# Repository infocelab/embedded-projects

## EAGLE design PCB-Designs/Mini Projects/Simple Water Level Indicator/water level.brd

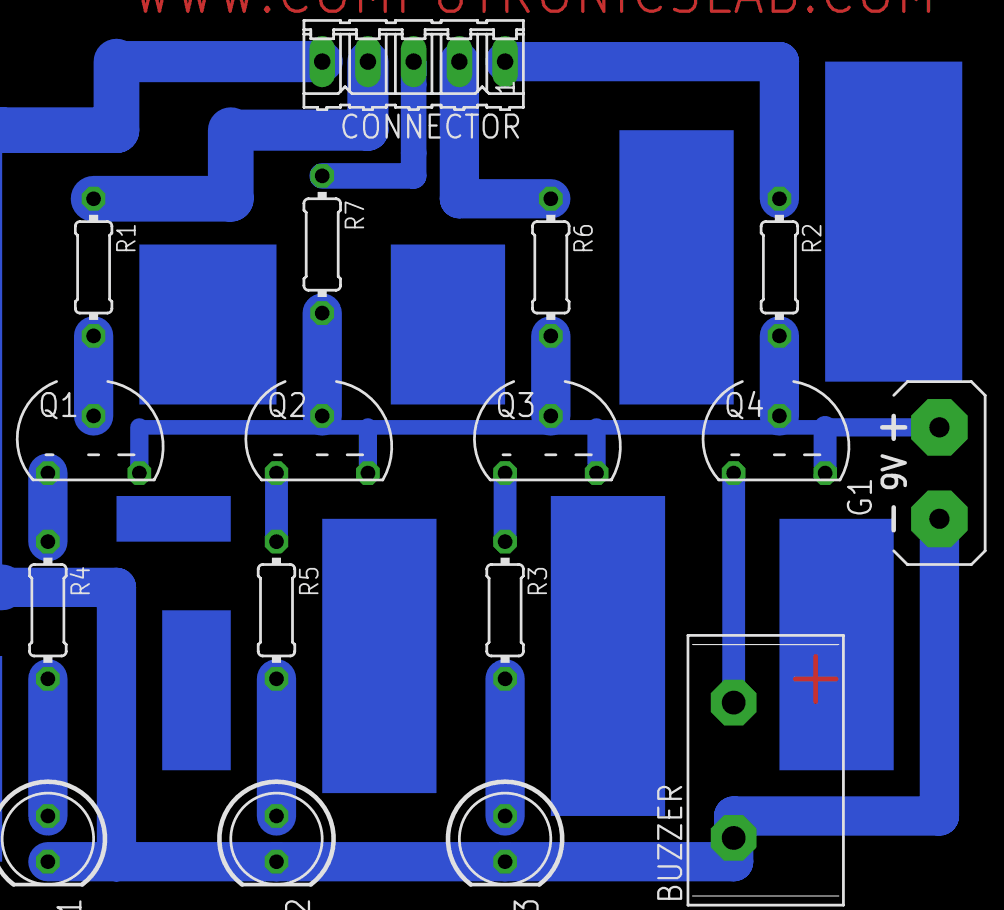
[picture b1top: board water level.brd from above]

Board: 2 copper layers, 17 parts (0 on the bottom side), 17 nets.

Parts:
BUZZER: B/C11S
CONNECTOR: 05P
G1: AB9V
LED1, LED2, LED3: 5mm; LED5MM
Q1, Q2, Q3, Q4: BC557; TO92
R1, R2, R3, R4, R5, R6, R7: 470E; 0204/7

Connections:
unnamed: Q1.3, R4.1
unnamed: Q2.3, R5.1
unnamed: Q3.3, R3.1
unnamed: Q1.2, R1.2
unnamed: Q2.2, R7.2
unnamed: Q3.2, R6.2
unnamed: Q4.2, R2.2
unnamed: BUZZER.2, Q4.3
unnamed: LED1.A, R4.2
unnamed: LED3.A, R3.2
unnamed: G1.+, Q1.1, Q2.1, Q3.1, Q4.1
unnamed: BUZZER.1, CONNECTOR.5, G1.-, LED1.K, LED2.K, LED3.K
unnamed: CONNECTOR.2, R6.1
unnamed: CONNECTOR.3, R7.1
unnamed: CONNECTOR.4, R1.1
unnamed: CONNECTOR.1, R2.1
unnamed: LED2.A, R5.2

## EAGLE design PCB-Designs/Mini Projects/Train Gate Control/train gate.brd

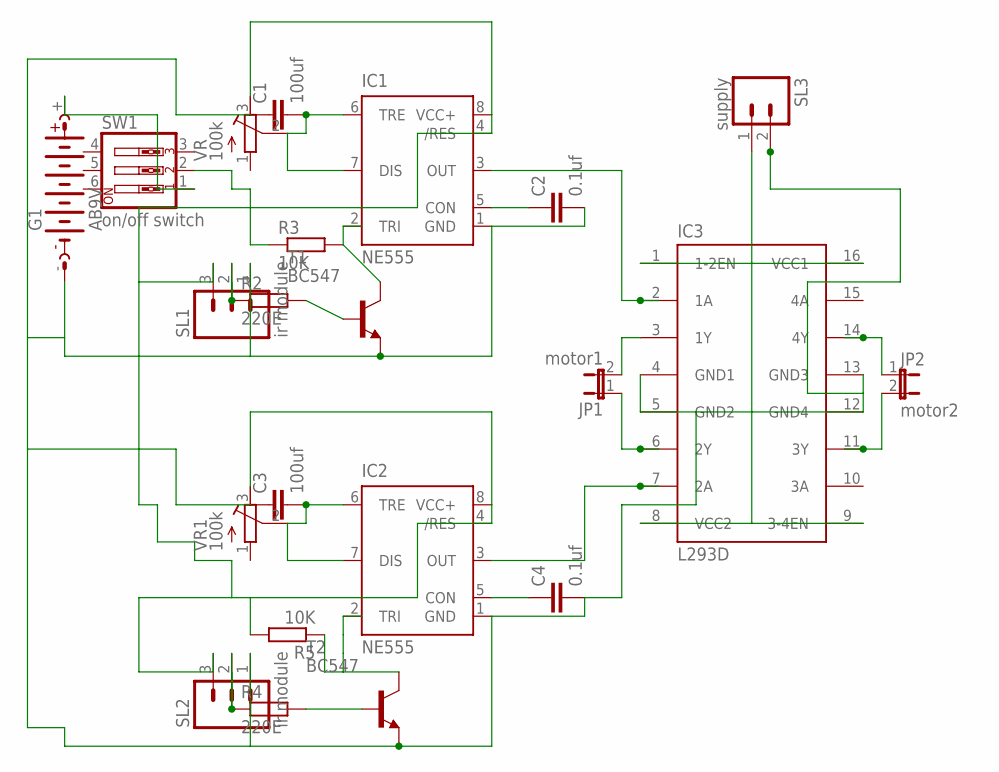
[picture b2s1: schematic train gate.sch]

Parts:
C1, C3: 100uf; C5B7.2
C2, C4: 0.1uf; C2.5-3
G1: AB9V
IC1, IC2: NE555; DIL-08
IC3: L293D; DIL16
JP1: motor1; JP1
JP2: motor2; JP1
R2, R4: 220E; 0204/7
R3, R5: 10K; 0204/7
SL1, SL2: ir module; 03P
SL3: supply; 02P
SW1: on/off switch; EDG-03
T1, T2: BC547; TO92
VR, VR1: 100k; RTRIM64P

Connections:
unnamed: C1.2, IC1.6 (TRE), IC1.7 (DIS), VR.2 (S)
unnamed: C3.2, IC2.6 (TRE), IC2.7 (DIS), VR1.2 (S)
unnamed: R2.1, SL1.2
unnamed: R4.1, SL2.2
unnamed: C2.1, IC1.5 (CON)
unnamed: R4.2, T2.2 (B)
unnamed: G1.+, SW1.1
unnamed: IC1.2 (TRI), R3.2, T1.3 (C)
unnamed: C4.1, IC2.5 (CON)
unnamed: IC2.2 (TRI), R5.1, T2.3 (C)
unnamed: C1.1, C2.2, C3.1, C4.2, G1.-, IC1.1 (GND), IC2.1 (GND), IC3.4 (GND1), IC3.5 (GND2), IC3.12 (GND4), IC3.13 (GND3), SL1.1, SL2.1, SL3.2, T1.1 (E), T2.1 (E)
unnamed: IC3.1 (1-2EN), IC3.8 (VCC2), IC3.9 (3-4EN), IC3.16 (VCC1), SL3.1
unnamed: IC1.4 (/RES), IC1.8 (VCC+), IC2.4 (/RES), IC2.8 (VCC+), R3.1, R5.2, SL1.3, SL2.3, SW1.2, VR.3 (A), VR1.3 (A)
unnamed: R2.2, T1.2 (B)
unnamed: IC3.3 (1Y), JP1.2
unnamed: IC3.6 (2Y), JP1.1
unnamed: IC3.14 (4Y), JP2.1
unnamed: IC3.11 (3Y), JP2.2
unnamed: IC1.3 (OUT), IC3.2 (1A)
unnamed: IC2.3 (OUT), IC3.7 (2A)

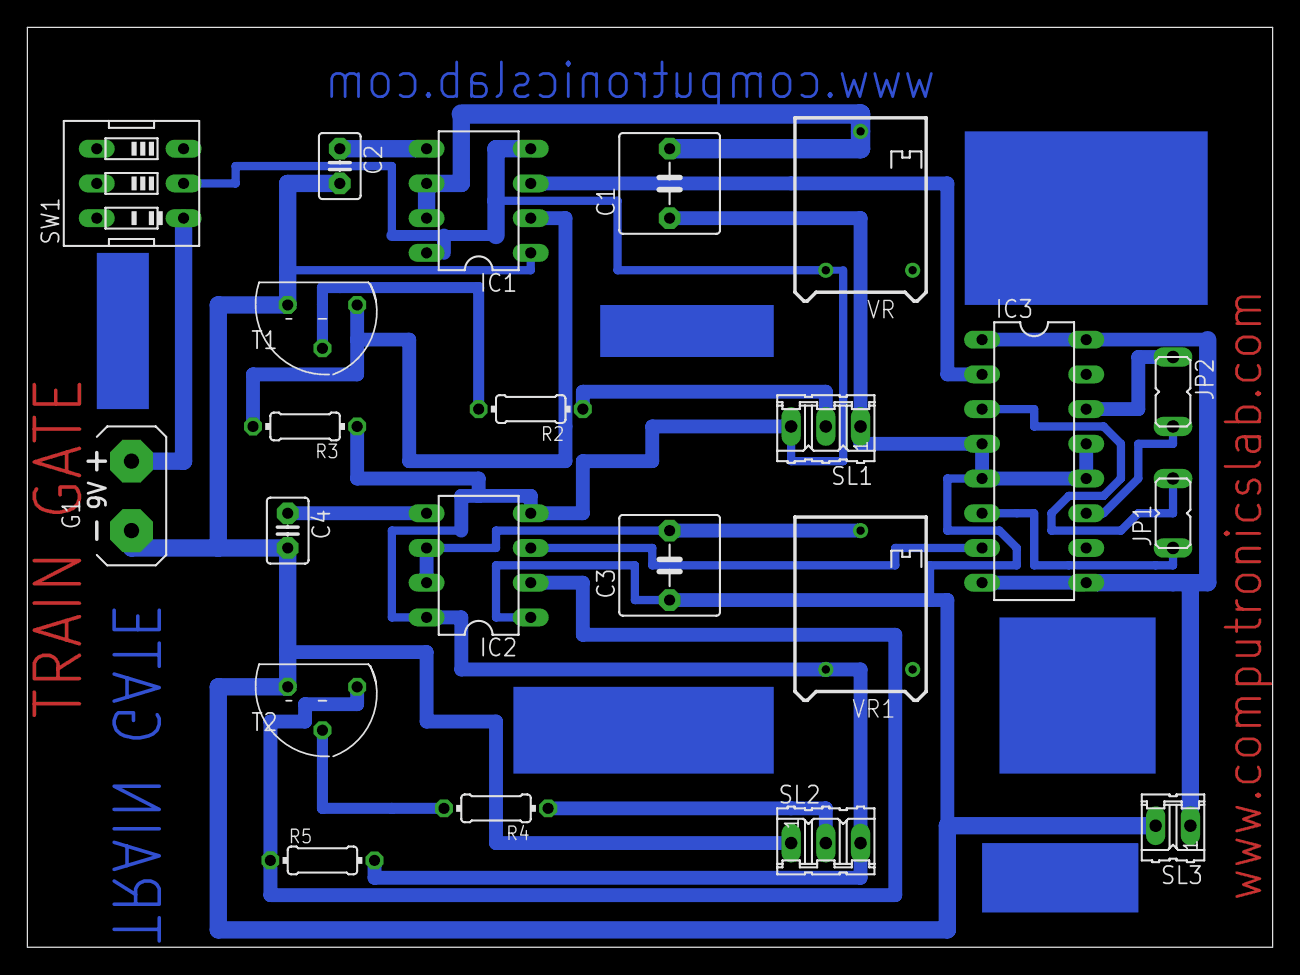
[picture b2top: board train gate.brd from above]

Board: 2 copper layers, 91.1 x 67.3 mm, 22 parts (0 on the bottom side), 20 nets.

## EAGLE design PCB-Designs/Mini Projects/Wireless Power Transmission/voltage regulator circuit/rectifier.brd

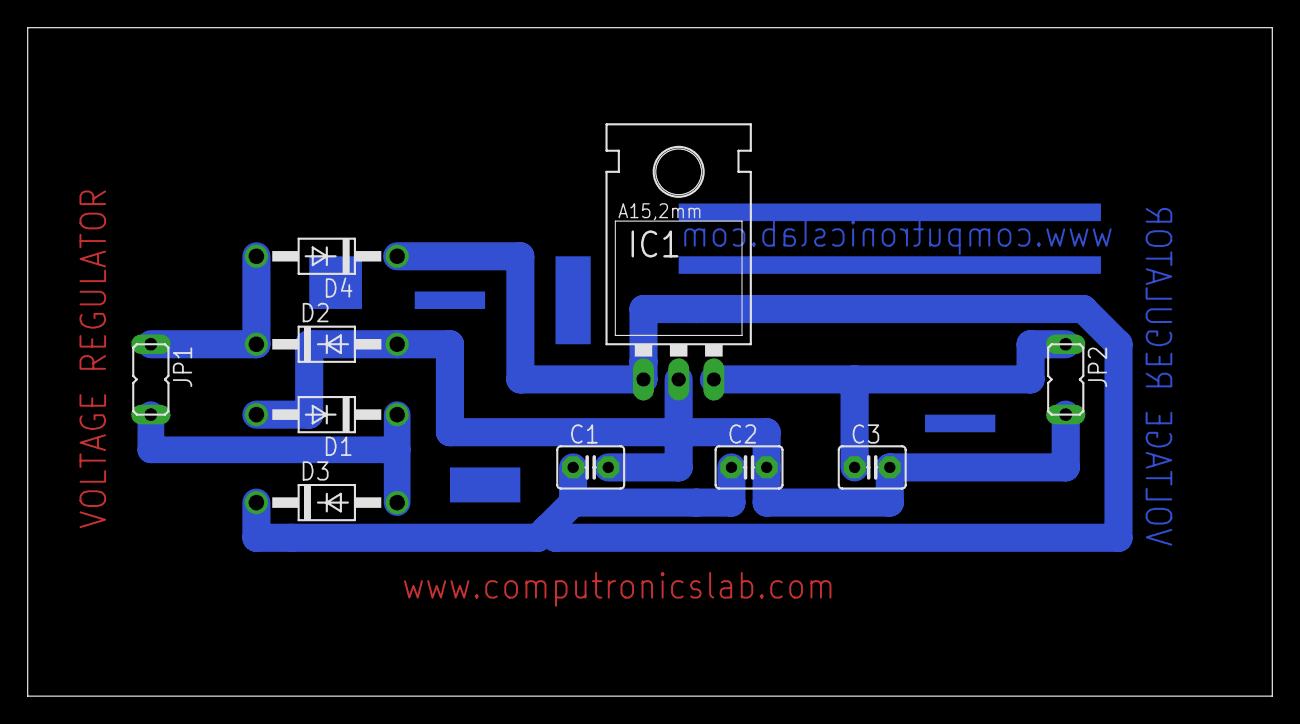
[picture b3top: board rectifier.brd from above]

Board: 2 copper layers, 89.8 x 48.2 mm, 10 parts (0 on the bottom side), 5 nets.

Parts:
C1: 47uf; C2.5-3
C2, C3: 0.1uf; C2.5-3
D1, D2, D3, D4: 1N4007; DO41-10
IC1: 7805; 78XXL
JP1: transformer; JP1
JP2: output; JP1

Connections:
unnamed: C1.2, C2.2, C3.2, D1.A, D2.A, IC1.GND, JP2.2
unnamed: C1.1, C2.1, D3.C, D4.C, IC1.IN
unnamed: D2.C, D4.A, JP1.1
unnamed: D1.C, D3.A, JP1.2
unnamed: C3.1, IC1.OUT, JP2.1

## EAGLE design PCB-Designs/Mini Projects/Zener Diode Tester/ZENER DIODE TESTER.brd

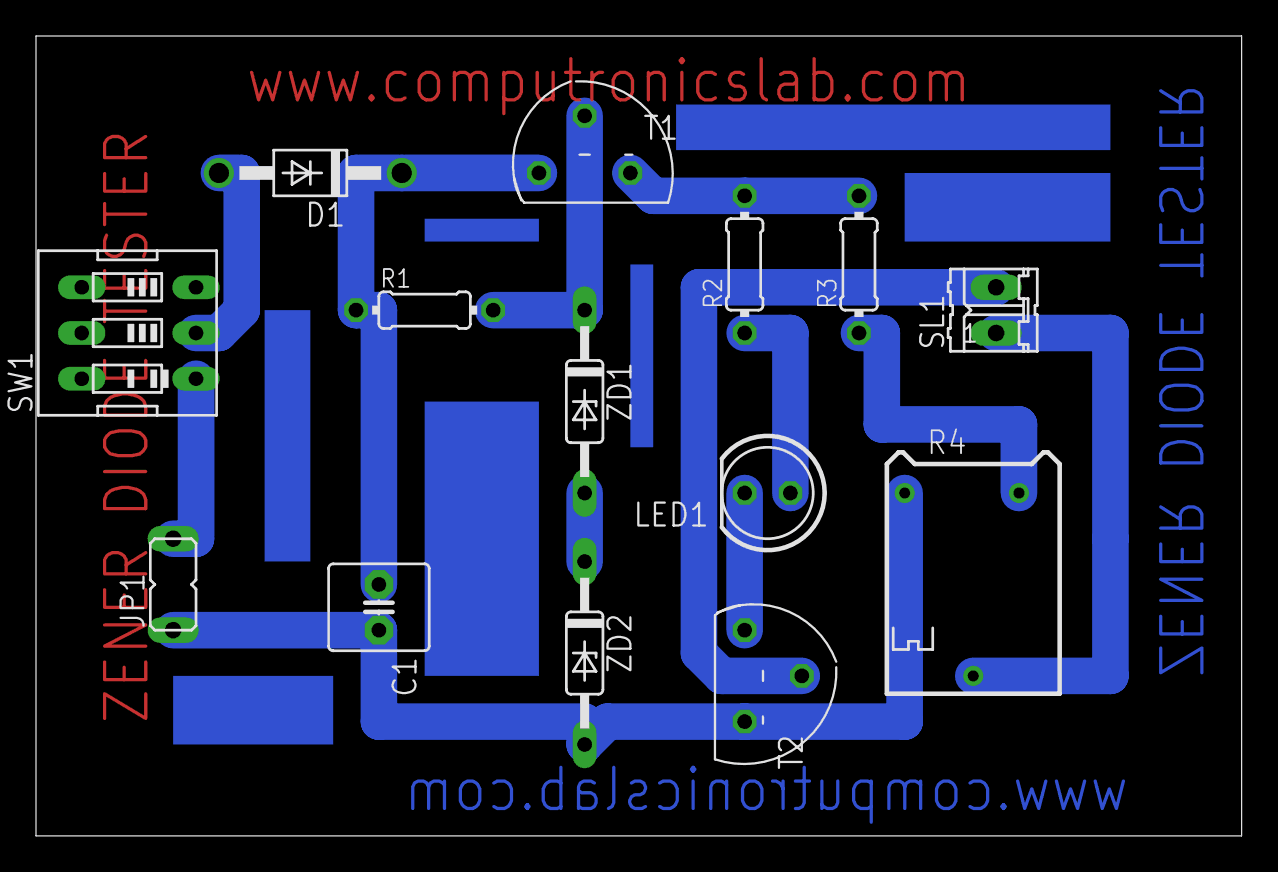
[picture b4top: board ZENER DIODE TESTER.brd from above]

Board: 2 copper layers, 67.0 x 44.4 mm, 14 parts (0 on the bottom side), 12 nets.

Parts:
C1: 220uf; C2.5-6
D1: 1N4007; DO41-10
JP1: transformer; JP1
LED1: 5mm; LED5MM
R1: 1K; 0204/7
R2: 1.5K; 0204/7
R3: 2.2K; 0204/7
R4: 47K; RTRIM64P
SL1: zener diode; 02P
SW1: on/off switch; EDG-03
T1, T2: BC547; TO92
ZD1, ZD2: 10V; DO35Z10

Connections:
unnamed: LED1.A, R2.1
unnamed: LED1.K, T2.3
unnamed: JP1.2, SW1.1
unnamed: D1.A, SW1.2
unnamed: C1.1, D1.C, R1.1, T1.3
unnamed: C1.2, JP1.1, R4.1, T2.1, ZD2.A
unnamed: R1.2, T1.2, ZD1.C
unnamed: ZD1.A, ZD2.C
unnamed: R2.2, R3.2, T1.1
unnamed: R3.1, R4.3
unnamed: SL1.2, T2.2
unnamed: R4.2, SL1.1

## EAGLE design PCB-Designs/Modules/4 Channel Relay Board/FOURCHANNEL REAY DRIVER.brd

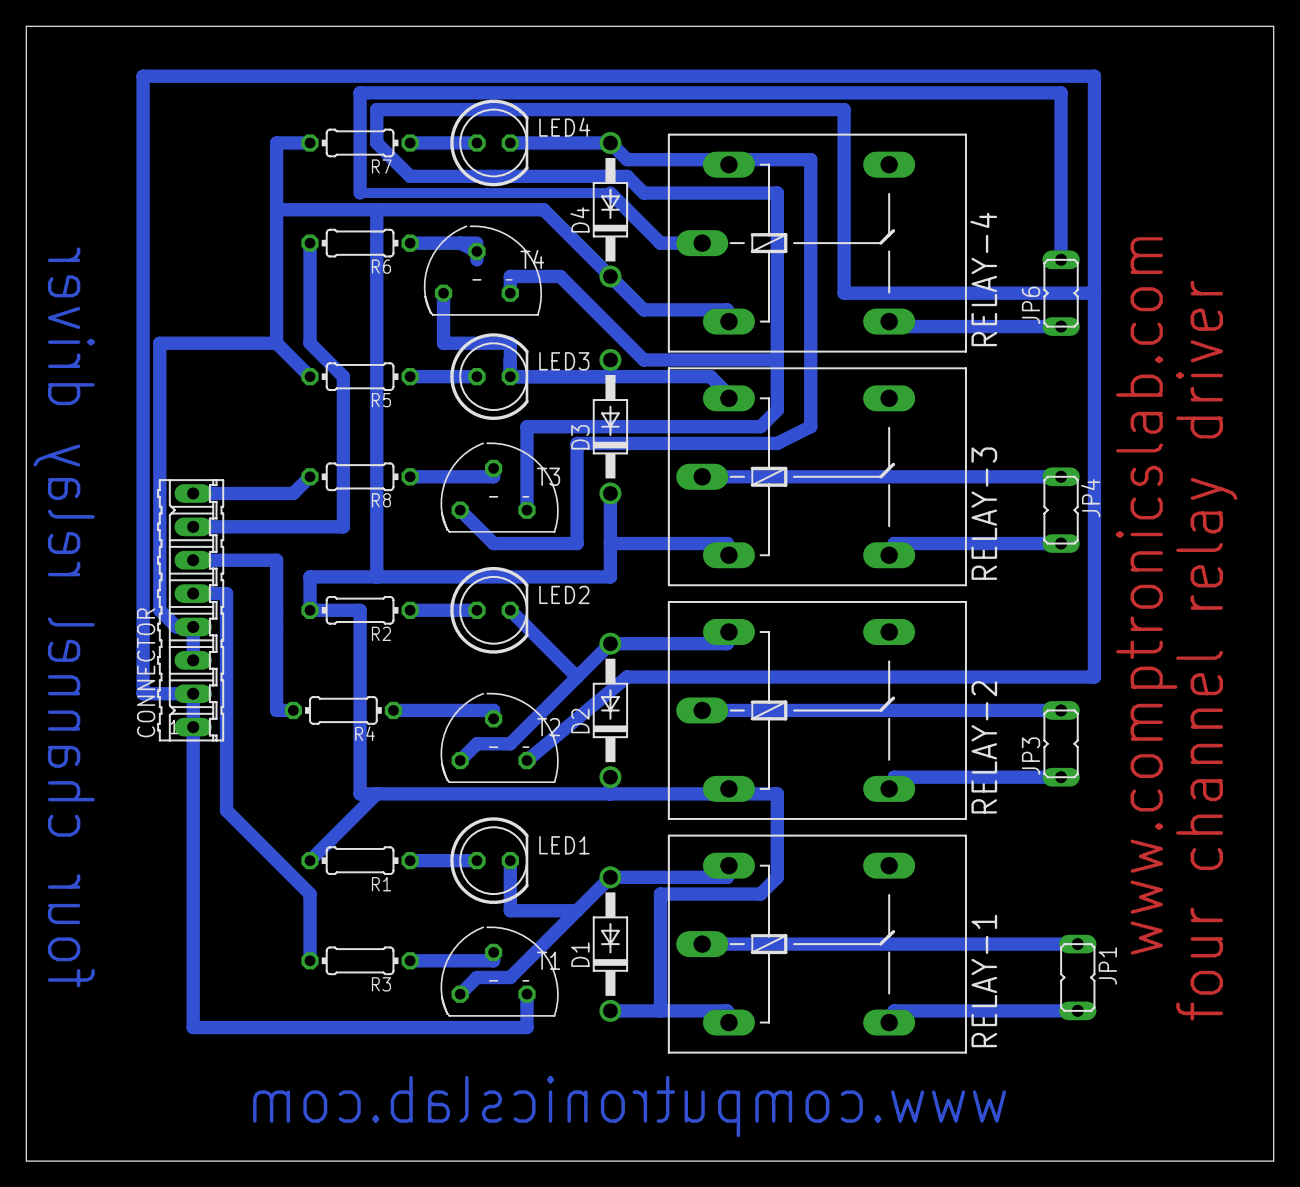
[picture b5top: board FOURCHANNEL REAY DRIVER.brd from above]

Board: 2 copper layers, 94.9 x 86.4 mm, 29 parts (0 on the bottom side), 26 nets.

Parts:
CONNECTOR: 8 PIN; 08P
D1, D2, D3, D4: 1N4007; DO41-10
JP1, JP3, JP4, JP6: AC CONNECTOR; JP1
LED1, LED2, LED3, LED4: 5MM; LED5MM
R1, R2, R5, R7: 1K; 0204/7
R3, R4, R6, R8: 5.6K; 0204/7
RELAY-1, RELAY-2, RELAY-3, RELAY-4: 12V; G5LE
T1, T2, T3, T4: BC547; TO92

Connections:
unnamed: D1.A, LED1.K, RELAY-1.2, T1.3
unnamed: D3.A, LED3.K, RELAY-3.2, T4.3
unnamed: CONNECTOR.3, CONNECTOR.4, D1.C, D2.C, D3.C, D4.C, R1.2, R2.2, R5.2, R7.2, RELAY-1.1, RELAY-2.1, RELAY-3.1, RELAY-4.1
unnamed: R4.1, T2.2
unnamed: R3.1, T1.2
unnamed: LED1.A, R1.1
unnamed: LED2.A, R2.1
unnamed: JP1.2, RELAY-1.S
unnamed: JP1.1, RELAY-1.P
unnamed: JP3.1, RELAY-2.S
unnamed: JP3.2, RELAY-2.P
unnamed: R8.1, T3.2
unnamed: CONNECTOR.5, R3.2
unnamed: CONNECTOR.6, R4.2
unnamed: R6.1, T4.2
unnamed: D2.A, LED2.K, RELAY-2.2, T2.3
unnamed: LED3.A, R5.1
unnamed: LED4.A, R7.1
unnamed: JP4.2, RELAY-3.S
unnamed: JP4.1, RELAY-3.P
unnamed: JP6.1, RELAY-4.S
unnamed: JP6.2, RELAY-4.P
unnamed: CONNECTOR.1, CONNECTOR.2, T1.1, T2.1, T3.1, T4.1
unnamed: CONNECTOR.7, R6.2
unnamed: CONNECTOR.8, R8.2
unnamed: D4.A, LED4.K, RELAY-4.2, T3.3

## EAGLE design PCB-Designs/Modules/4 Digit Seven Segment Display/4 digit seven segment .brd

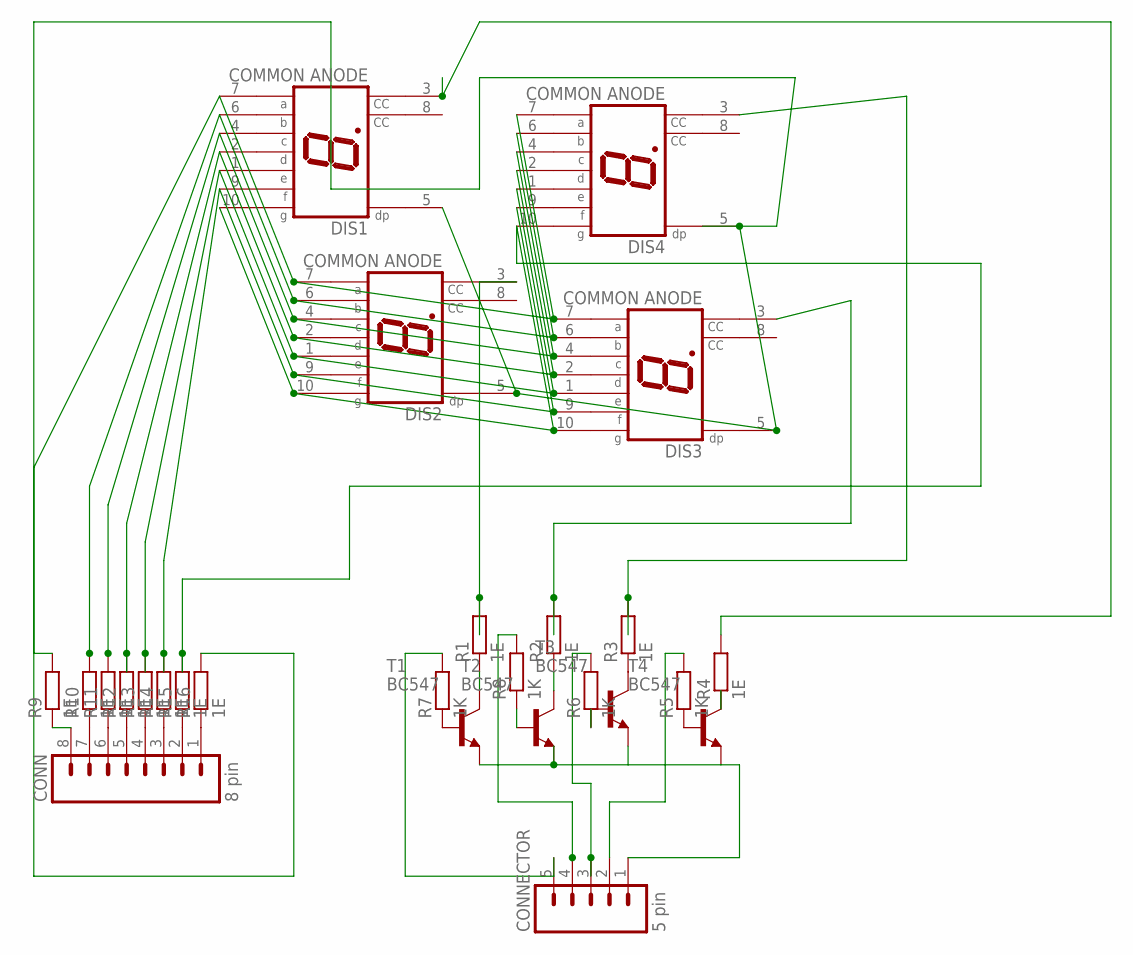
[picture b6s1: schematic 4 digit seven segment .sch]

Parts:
CONN: 8 pin; 08P
CONNECTOR: 5 pin; 05P
DIS1, DIS2, DIS3, DIS4: COMMON ANODE; HDSP-M
R1, R2, R3, R4, R9, R10, R11, R12, R13, R14, R15, R16: 1E; 0204/7
R5, R6, R7, R8: 1K; 0204/7
T1, T2, T3, T4: BC547; TO92

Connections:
unnamed: CONNECTOR.4, R8.2
unnamed: DIS1.9 (F), DIS2.9 (F), DIS3.9 (F), DIS4.9 (F), R14.2
unnamed: DIS1.2 (D), DIS2.2 (D), DIS3.2 (D), DIS4.2 (D), R12.2
unnamed: DIS1.6 (B), DIS2.6 (B), DIS3.6 (B), DIS4.6 (B), R10.2
unnamed: DIS1.7 (A), DIS2.7 (A), DIS3.7 (A), DIS4.7 (A), R9.2
unnamed: DIS3.3 (CC), R2.2
unnamed: DIS1.4 (C), DIS2.4 (C), DIS3.4 (C), DIS4.4 (C), R11.2
unnamed: DIS1.1 (E), DIS2.1 (E), DIS3.1 (E), DIS4.1 (E), R13.2
unnamed: CONNECTOR.3, R6.2
unnamed: R1.1, T1.3 (C)
unnamed: R2.1, T2.3 (C)
unnamed: R3.1, T3.3 (C)
unnamed: R4.1, T4.3 (C)
unnamed: R5.1, T4.2 (B)
unnamed: R6.1, T3.2 (B)
unnamed: R7.1, T1.2 (B)
unnamed: R8.1, T2.2 (B)
unnamed: CONN.8, R9.1
unnamed: CONN.7, R10.1
unnamed: CONN.6, R11.1
unnamed: CONN.4, R13.1
unnamed: CONN.3, R14.1
unnamed: CONN.2, R15.1
unnamed: CONN.1, R16.1
unnamed: CONN.5, R12.1
unnamed: DIS1.10 (G), DIS2.10 (G), DIS3.10 (G), DIS4.10 (G), R15.2
unnamed: DIS1.5 (DP), DIS2.5 (DP), DIS3.5 (DP), DIS4.5 (DP), R16.2
unnamed: CONNECTOR.5, R7.2
unnamed: CONNECTOR.2, R5.2
unnamed: CONNECTOR.1, T1.1 (E), T2.1 (E), T3.1 (E), T4.1 (E)
unnamed: DIS1.3 (CC), R4.2
unnamed: DIS4.3 (CC), R3.2
unnamed: DIS2.3 (CC), R1.2

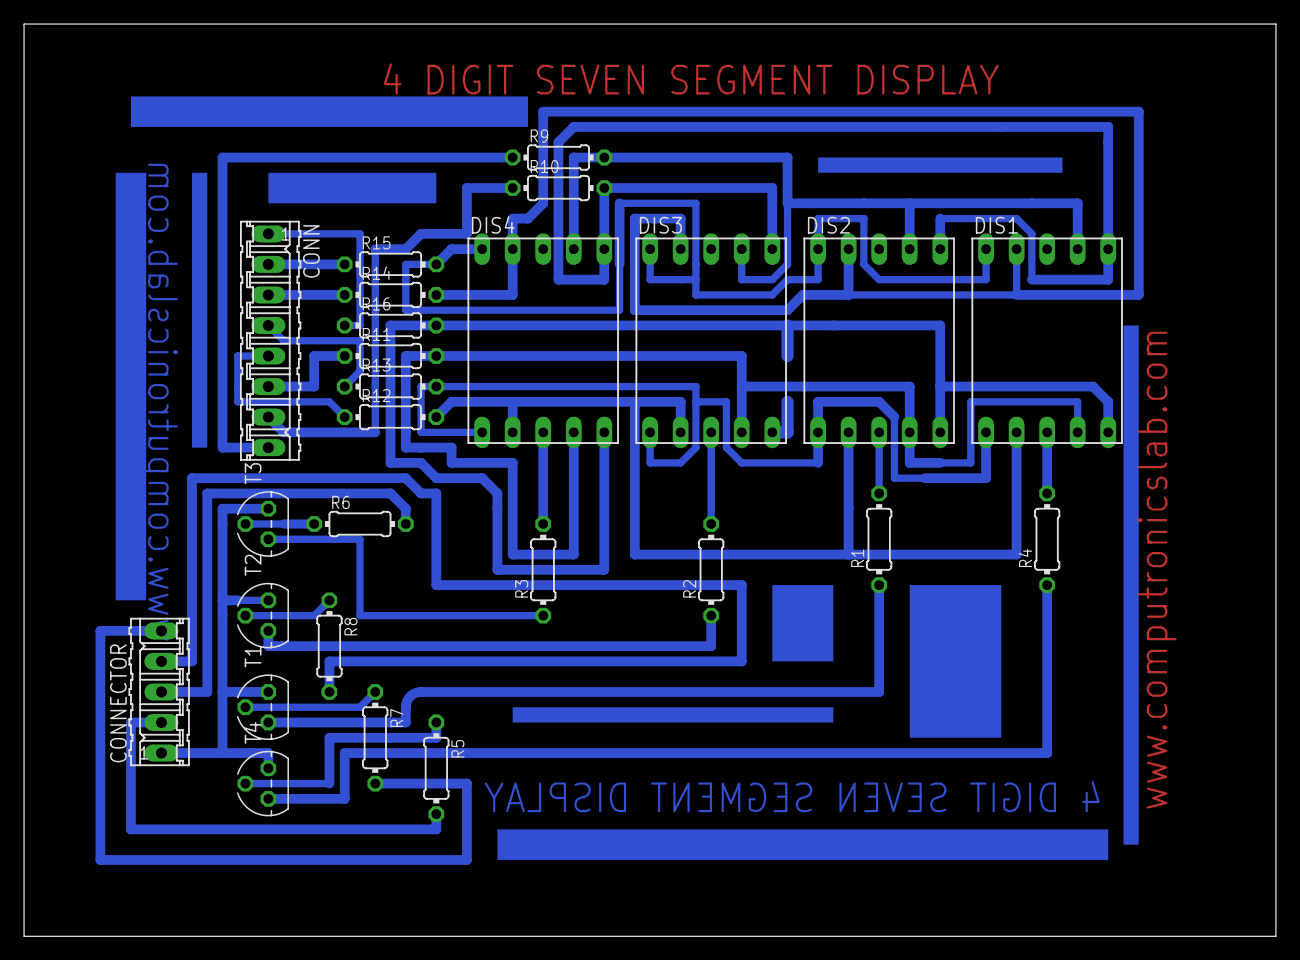
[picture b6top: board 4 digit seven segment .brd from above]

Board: 2 copper layers, 104.1 x 75.9 mm, 26 parts (0 on the bottom side), 33 nets.

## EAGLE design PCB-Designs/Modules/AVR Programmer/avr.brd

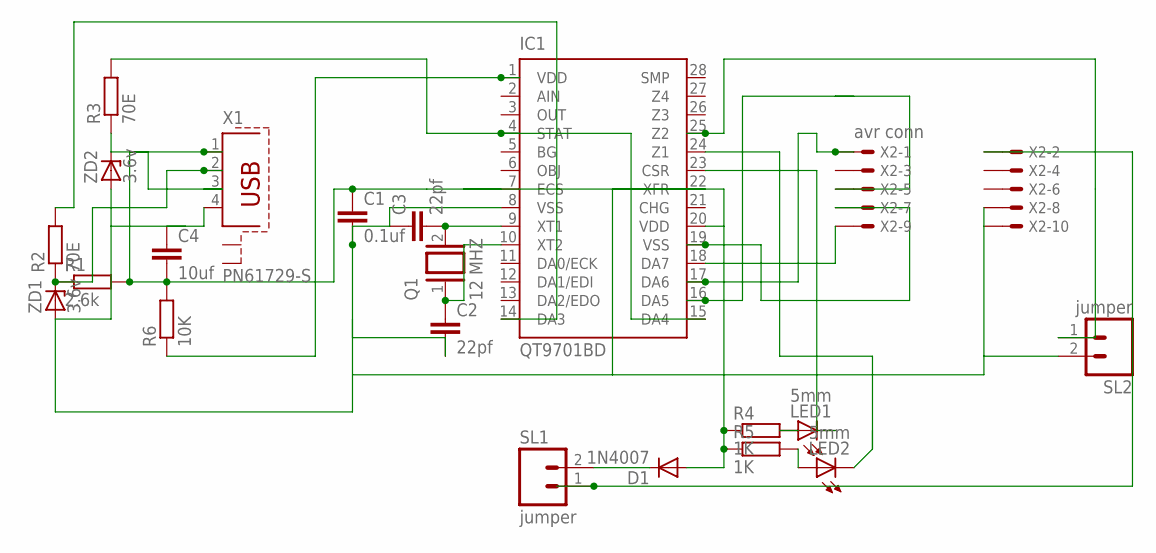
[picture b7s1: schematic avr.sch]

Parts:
C1: 0.1uf; C2.5-3
C2, C3: 22pf; C2.5-3
C4: 10uf; C2.5-3
D1: 1N4007; DO41-10
IC1: QT9701BD; DIL28-3
LED1, LED2: 5mm; LED5MM
Q1: 12 MHZ; QS
R1: 2.6k; 0204/7
R2, R3: 70E; 0204/7
R4, R5: 1K; 0204/7
R6: 10K; 0204/7
SL1, SL2: jumper; 02P
X1: PN61729-S
X2: avr conn; 057-010-1
ZD1, ZD2: 3.6v; SOD81

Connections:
unnamed: C3.2, IC1.9 (XT1), Q1.2
unnamed: C2.1, IC1.10 (XT2), Q1.1
unnamed: IC1.1 (VDD), R6.1
unnamed: R1.1, R2.1, X1.2, ZD1.C
unnamed: C1.2, C2.2, C3.1, C4.1, IC1.8 (VSS), IC1.22 (XFR), SL2.2, X1.4, X2.8, X2.10, ZD1.A, ZD2.A
unnamed: IC1.14 (DA3), R2.2
unnamed: R3.1, X1.3, ZD2.C
unnamed: IC1.4 (STAT), IC1.15 (DA4), R3.2
unnamed: C1.1, C4.2, D1.A, IC1.7 (ECS), IC1.20 (VDD), R1.2, R4.1, R5.1, R6.2, X1.1
unnamed: IC1.24 (Z1), LED2.K (C)
unnamed: D1.C, SL1.2
unnamed: IC1.23 (CSR), LED1.K (C)
unnamed: LED2.A, R5.2
unnamed: SL1.1, X2.2
unnamed: IC1.17 (DA6), X2.1
unnamed: IC1.16 (DA5), X2.5
unnamed: IC1.19 (VSS), X2.7
unnamed: IC1.18 (DA7), X2.9
unnamed: IC1.25 (Z2), SL2.1
unnamed: LED1.A, R4.2

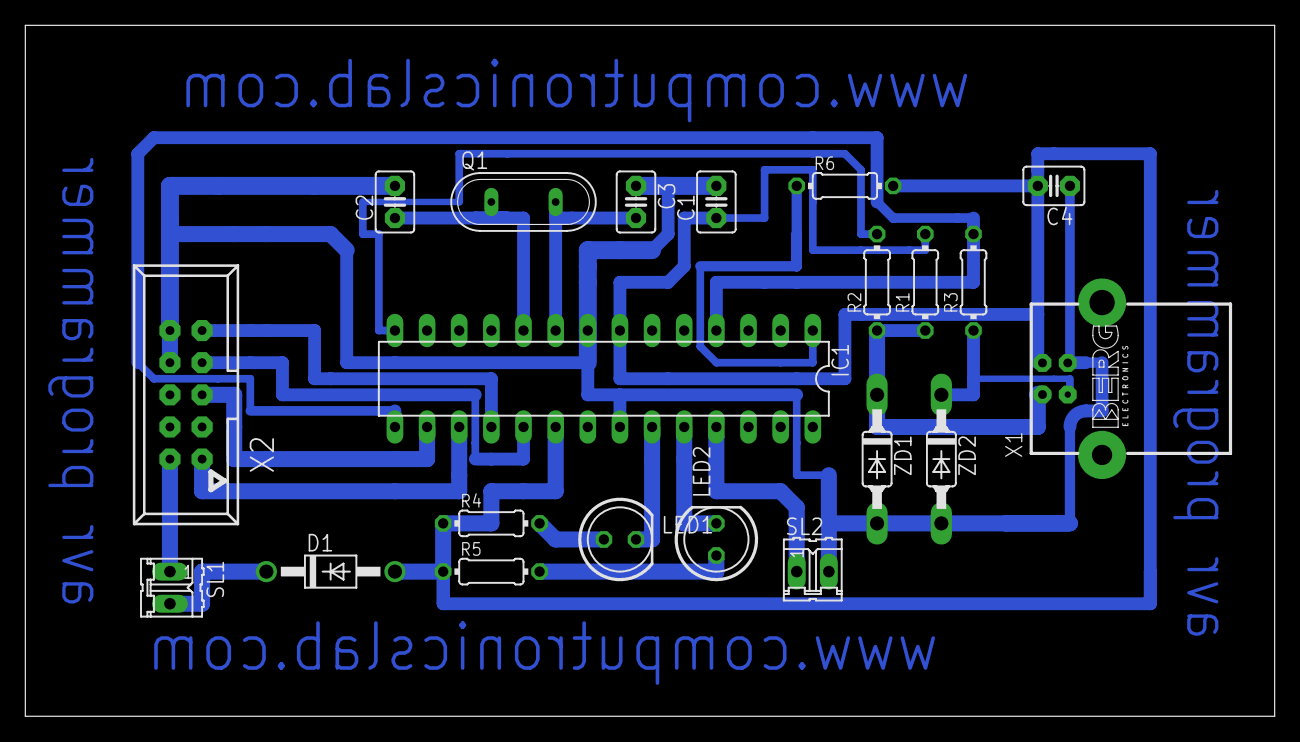
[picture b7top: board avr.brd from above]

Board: 2 copper layers, 98.7 x 54.6 mm, 21 parts (0 on the bottom side), 20 nets.
